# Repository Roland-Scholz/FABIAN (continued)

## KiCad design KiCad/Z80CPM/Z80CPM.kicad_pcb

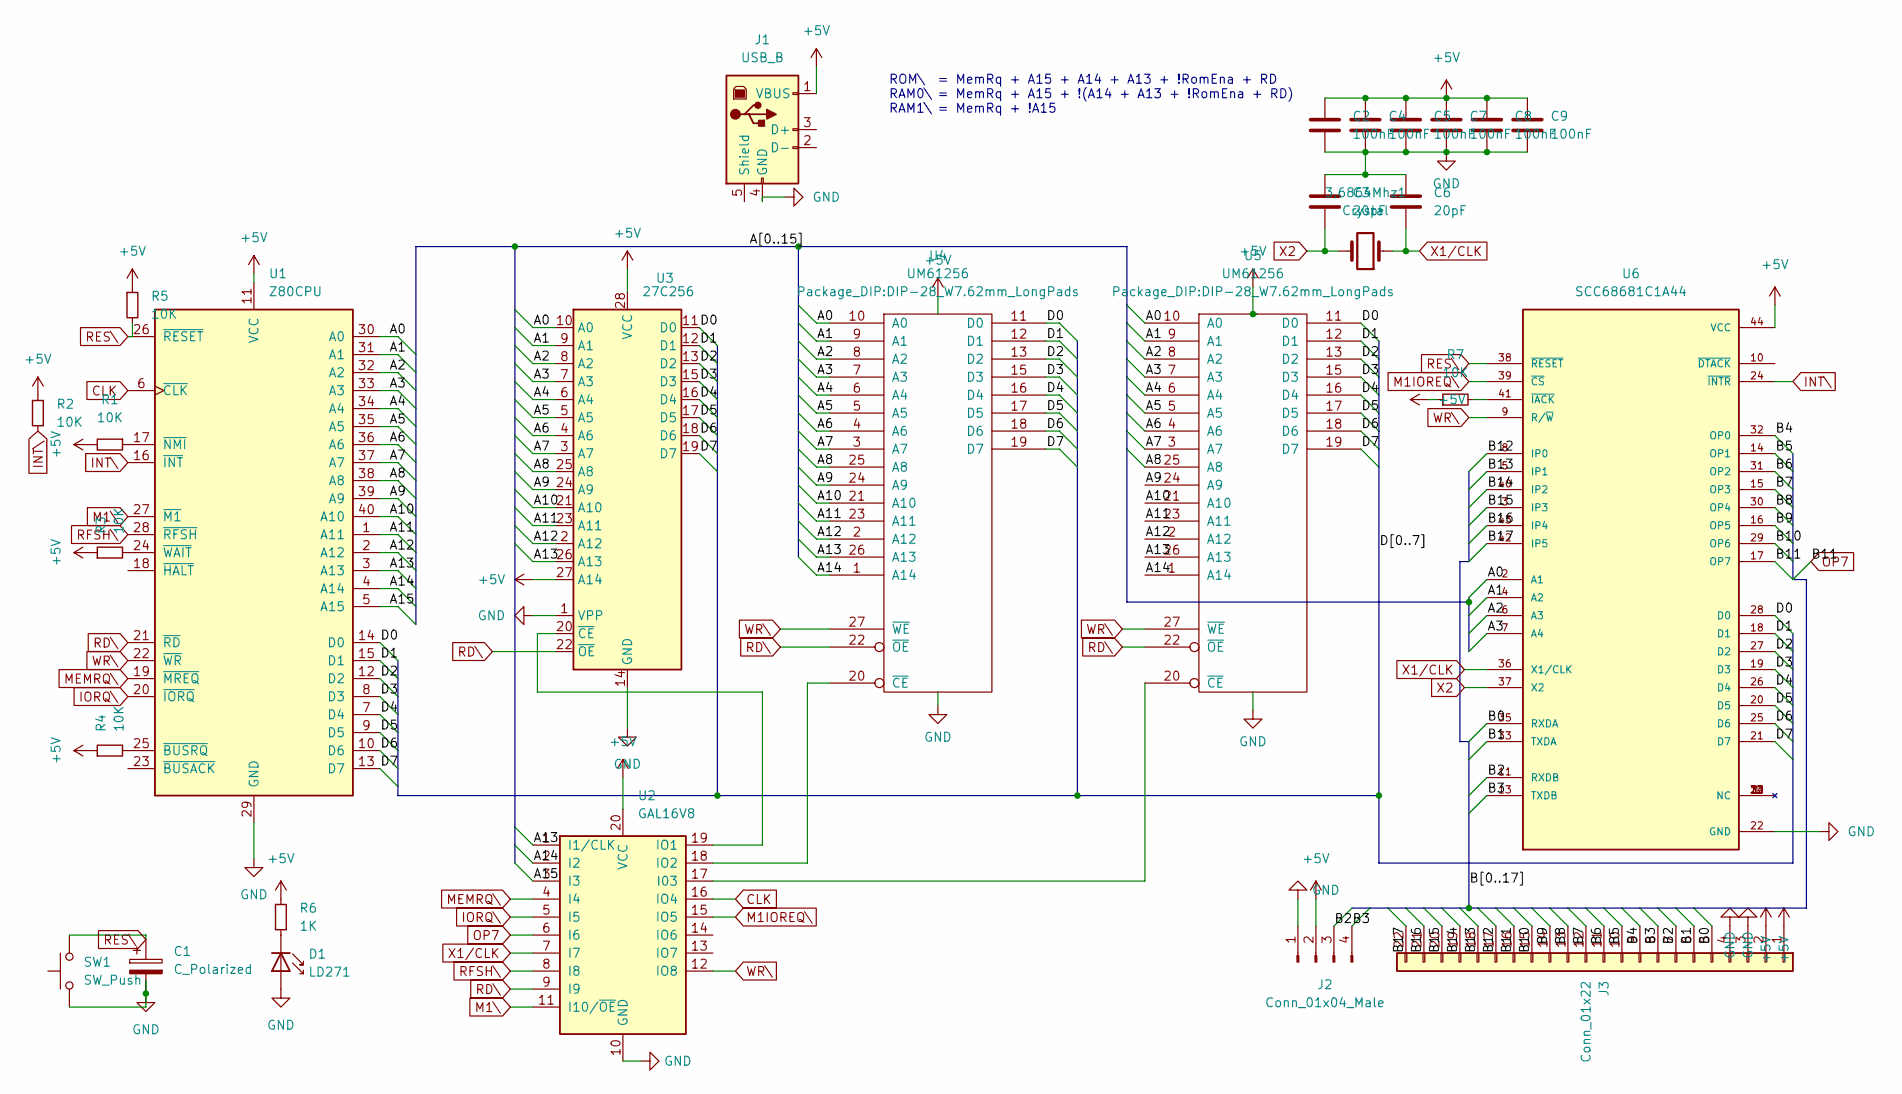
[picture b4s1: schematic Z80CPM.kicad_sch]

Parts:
3,6864Mhz1: Crystal; Crystal_HC18-U_Vertical
C1: C_Polarized; CP_Radial_D5.0mm_P2.50mm
C2, C4, C5, C7, C8, C9: 100nF; PinHeader_1x02_P2.54mm_Vertical
C3, C6: 20pF; PinHeader_1x02_P2.54mm_Vertical
D1: LD271; LED_D5.0mm_IRGrey
J1: USB_B; USB_B_Lumberg_2411_02_Horizontal
J2: Conn_01x04_Male; PinHeader_1x04_P2.54mm_Vertical
J3: Conn_01x22; PinHeader_1x22_P2.54mm_Vertical
R1, R2, R3, R4, R5, R7: 10K; R_Axial_DIN0207_L6.3mm_D2.5mm_P10.16mm_Horizontal
R6: 1K; R_Axial_DIN0204_L3.6mm_D1.6mm_P1.90mm_Vertical
SW1: SW_Push; C_Rect_L7.5mm_W6.5mm_P5.00mm
U1: Z80CPU; DIP-40_W15.24mm_Socket_LongPads
U2: GAL16V8; DIP-20_W7.62mm_Socket_LongPads
U3: 27C256; DIP-28_W15.24mm
U4, U5: UM61256; DIP-28_W7.62mm_LongPads
U6: SCC68681C1A44; PLCC-44_THT-Socket; PARTREV _1

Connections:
+5V: C2.1, C4.1, C5.1, C7.1, C8.1, C9.1, J1.1 (VBUS), J2.2, J3.1, J3.2, R1.2, R2.1, R3.1, R4.1, R5.1, R6.1, R7.1, U1.11 (VCC), U2.20 (VCC), U3.27 (A14), U3.28 (VCC), U4.28 (VCC), U5.28 (VCC), U6.44 (VCC)
/A0: U1.30 (A0), U3.10 (A0), U4.10 (A0), U5.10 (A0), U6.2 (A1)
/A1: U1.31 (A1), U3.9 (A1), U4.9 (A1), U5.9 (A1), U6.4 (A2)
/A2: U1.32 (A2), U3.8 (A2), U4.8 (A2), U5.8 (A2), U6.6 (A3)
/A3: U1.33 (A3), U3.7 (A3), U4.7 (A3), U5.7 (A3), U6.7 (A4)
/A4: U1.34 (A4), U3.6 (A4), U4.6 (A4), U5.6 (A4)
/A5: U1.35 (A5), U3.5 (A5), U4.5 (A5), U5.5 (A5)
/A6: U1.36 (A6), U3.4 (A6), U4.4 (A6), U5.4 (A6)
/A7: U1.37 (A7), U3.3 (A7), U4.3 (A7), U5.3 (A7)
/A8: U1.38 (A8), U3.25 (A8), U4.25 (A8), U5.25 (A8)
/A9: U1.39 (A9), U3.24 (A9), U4.24 (A9), U5.24 (A9)
/A10: U1.40 (A10), U3.21 (A10), U4.21 (A10), U5.21 (A10)
/A11: U1.1 (A11), U3.23 (A11), U4.23 (A11), U5.23 (A11)
/A12: U1.2 (A12), U3.2 (A12), U4.2 (A12), U5.2 (A12)
/A13: U1.3 (A13), U2.1 (I1/CLK), U3.26 (A13), U4.26 (A13), U5.26 (A13)
/A14: U1.4 (A14), U2.2 (I2), U4.1 (A14), U5.1 (A14)
/A15: U1.5 (A15), U2.3 (I3)
/B0: J3.5, U6.35 (RXDA)
/B1: J3.6, U6.33 (TXDA)
/B2: J2.3, J3.7, U6.11 (RXDB)
/B3: J2.4, J3.8, U6.13 (TXDB)
/B4: J3.9, U6.32 (OP0)
/B5: J3.10, U6.14 (OP1)
/B6: J3.11, U6.31 (OP2)
/B7: J3.12, U6.15 (OP3)
/B8: J3.13, U6.30 (OP4)
/B9: J3.14, U6.16 (OP5)
/B10: J3.15, U6.29 (OP6)
/B12: J3.17, U6.8 (IP0)
/B13: J3.18, U6.5 (IP1)
/B14: J3.19, U6.40 (IP2)
/B15: J3.20, U6.3 (IP3)
/B16: J3.21, U6.43 (IP4)
/B17: J3.22, U6.42 (IP5)
/D0: U1.14 (D0), U3.11 (D0), U4.11 (D0), U5.11 (D0), U6.28 (D0)
/D1: U1.15 (D1), U3.12 (D1), U4.12 (D1), U5.12 (D1), U6.18 (D1)
/D2: U1.12 (D2), U3.13 (D2), U4.13 (D2), U5.13 (D2), U6.27 (D2)
/D3: U1.8 (D3), U3.15 (D3), U4.15 (D3), U5.15 (D3), U6.19 (D3)
/D4: U1.7 (D4), U3.16 (D4), U4.16 (D4), U5.16 (D4), U6.26 (D4)
/D5: U1.9 (D5), U3.17 (D5), U4.17 (D5), U5.17 (D5), U6.20 (D5)
/D6: U1.10 (D6), U3.18 (D6), U4.18 (D6), U5.18 (D6), U6.25 (D6)
/D7: U1.13 (D7), U3.19 (D7), U4.19 (D7), U5.19 (D7), U6.21 (D7)
CLK: U1.6 (~CLK), U2.16 (IO4)
GND: C1.2, C2.2, C3.1, C4.2, C5.2, C6.1, C7.2, C8.2, C9.2, D1.2 (A), J1.4 (GND), J2.1, J3.3, J3.4, SW1.1, U1.29 (GND), U2.10 (GND), U3.1 (VPP), U3.14 (GND), U4.14 (GND), U5.14 (GND), U6.22 (GND)
INT\: R2.2, U1.16 (~INT), U6.24 (~INTR)
IORQ\: U1.20 (~IORQ), U2.5 (I5)
M1IOREQ\: U2.15 (IO5), U6.39 (~CS)
M1\: U1.27 (~M1), U2.11 (I10/~OE)
MEMRQ\: U1.19 (~MREQ), U2.4 (I4)
unnamed: D1.1 (K), R6.2
unnamed: R3.2, U1.24 (~WAIT)
unnamed: R4.2, U1.25 (~BUSRQ)
unnamed: R7.2, U6.41 (~IACK)
unnamed: R1.1, U1.17 (~NMI)
unnamed: U2.17 (I03), U5.20 (~CE)
unnamed: U2.18 (IO2), U4.20 (~CE)
unnamed: U2.19 (IO1), U3.20 (~CE)
OP7: J3.16, U2.6 (I6), U6.17 (OP7)
RD\: U1.21 (~RD), U2.9 (I9), U3.22 (~OE), U4.22 (~OE), U5.22 (~OE)
RES\: C1.1, R5.2, SW1.2, U1.26 (~RESET), U6.38 (~RESET)
RFSH\: U1.28 (~RFSH), U2.8 (I8)
WR\: U1.22 (~WR), U2.12 (IO8), U4.27 (~WE), U5.27 (~WE), U6.9 (R/~W)
X1/CLK: 3,6864Mhz1.1, C6.2, U2.7 (I7), U6.36 (X1/CLK)
X2: 3,6864Mhz1.2, C3.2, U6.37 (X2)

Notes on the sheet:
ROM\ = MemRq + A15 + A14 + A13 + !RomEna + RD RAM0\ = MemRq + A15 + !(A14 + A13 + !RomEna + RD) RAM1\ = MemRq + !A15

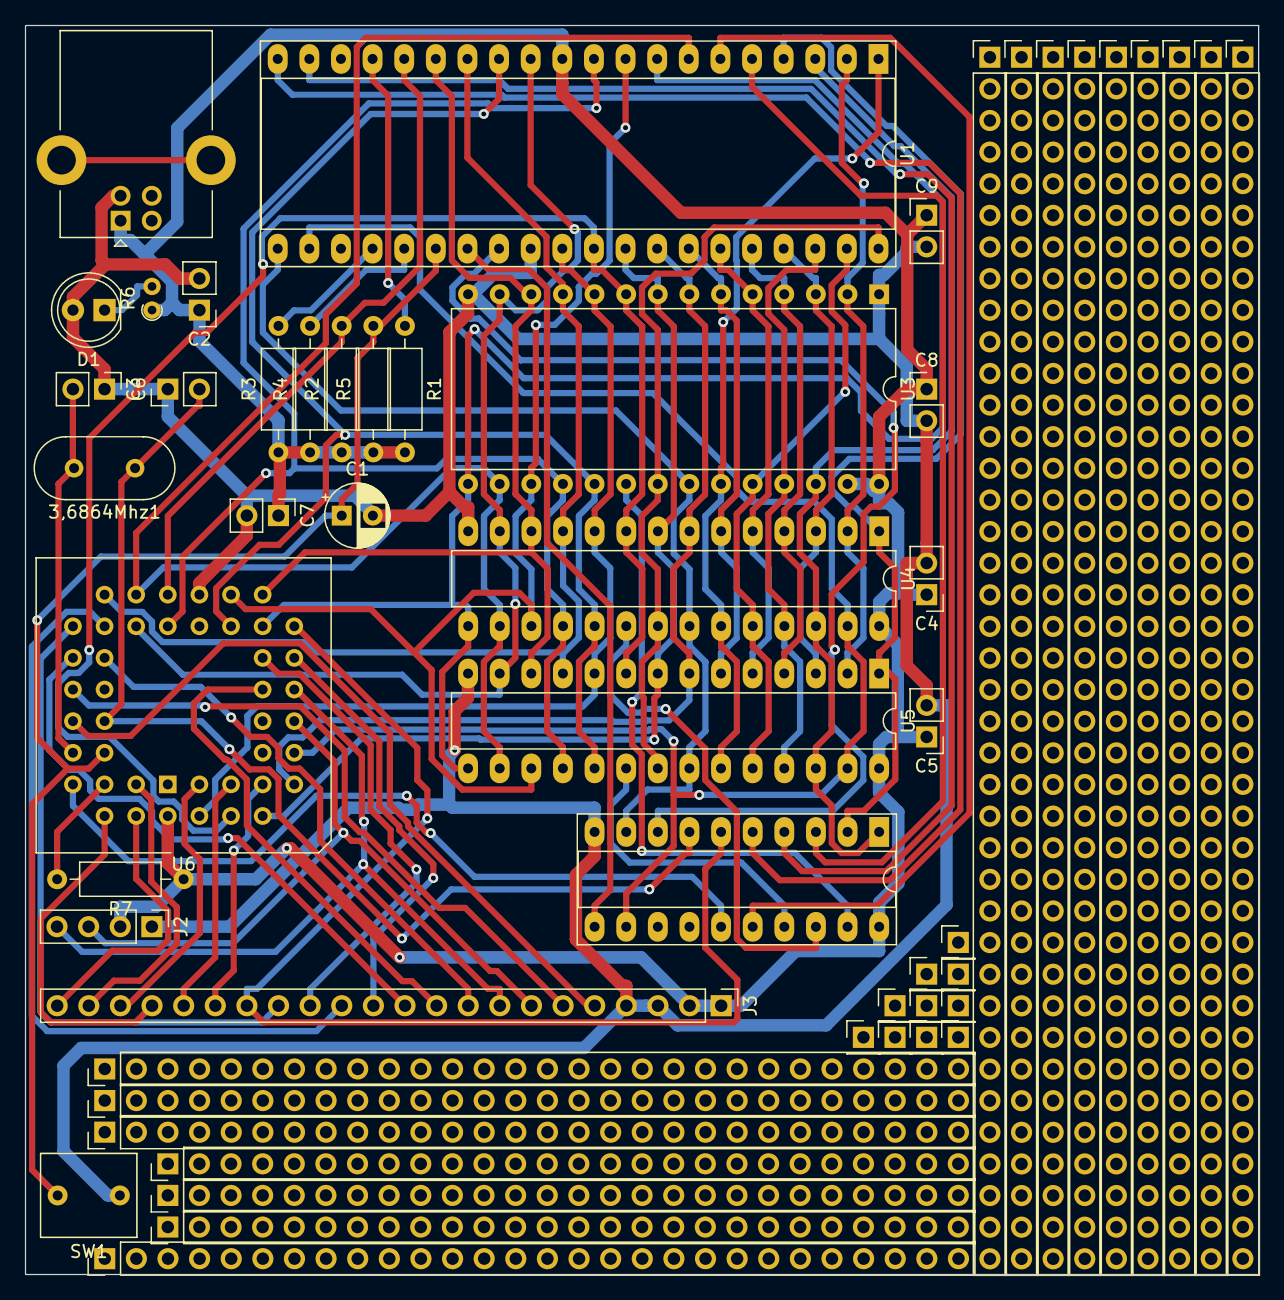
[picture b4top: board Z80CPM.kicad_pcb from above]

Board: 2 copper layers, 99.1 x 100.3 mm, 28 parts (0 on the bottom side), 64 nets.

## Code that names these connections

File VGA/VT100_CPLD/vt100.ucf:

#PACE: Start of Constraints generated by PACE

#PACE: Start of PACE I/O Pin Assignments
#NET "OE_DAT"	SLOW;
#NET "OE_ADR"	SLOW;
#NET "OE_RAM"	SLOW;
#NET "LOADDAT"	SLOW;
#NET "LOADAD"	SLOW;
#NET "OE_RAM"	SLOW;
#NET "WE_RAM"	SLOW;
#NET "CHAROE"	SLOW;
#NET "CRTCOE"	SLOW;

NET "HSYNC"		LOC = "P1";
NET "A15"		LOC = "P2";
NET "WR"			LOC = "P3";
NET "RD"			LOC = "P4";
NET "PCLK"  	LOC = "P5"; 
NET "LOADDAT" 	LOC = "P6"; 
NET "LOADCOLB"	LOC = "P7"; 
NET "LOADAD"	LOC = "P8"; 
NET "CCLK"		LOC = "P9"; 
NET "DE"			LOC = "P11"; 
NET "HS"			LOC = "P12"; 
NET "VS"			LOC = "P13"; 
NET "LOADSR"	LOC = "P14"; 
NET "CRTCOE"	LOC = "P18"; 
NET "WE_RAM"	LOC = "P19"; 
NET "LOADCHR"	LOC = "P20"; 
NET "CHAROE"	LOC = "P22"; 
NET "DISPEN"	LOC = "P24"; 
NET "OE_ADR"	LOC = "P25";
NET "LOADCOL"	LOC = "P26";
NET "OE_DAT"	LOC = "P27";
NET "OE_RAM"	LOC = "P28";
#NET "T0"			LOC = "P29";
#NET "CE_RAM"	LOC = "P33";

NET "VSYNC"		LOC = "P44";
NET "PIXCLKO"	LOC = "P43";
NET "LCHRLINE" LOC = "P42";
NET "LOADSRIN" LOC = "P40";

#PACE: Start of PACE Area Constraints

#PACE: Start of PACE Prohibit Constraints

#PACE: End of Constraints generated by PACE

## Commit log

2022-04-29 readme
2022-04-29 more pics
2022-04-29 tidy up
2022-04-29 datasheets
2022-04-29 WinCUPL
2022-04-29 pcb bottom
2022-04-29 email
2023-01-10 typo
2023-03-14 include
2023-05-03 VGA + SDCard
2023-06-09 VT100 MCU, KiCad and CPLD
2023-06-10 OE_ADR
2023-09-29 vt100
2023-09-29 mcu+graph
2023-10-09 mode mode Please enter the commit message for your changes. Lines starting
2023-10-09 mode
2024-02-03 Vt102 complete
2024-02-03 vt102 tidy-up
2024-02-03 invert wrap function
2024-02-03 cycle default color
2024-05-28 ADM-3A
2024-05-28 rolmon
